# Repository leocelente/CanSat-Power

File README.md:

# CanSat - Power Board
## Introduction
These are the design files for the CanSat power distribution board
## Content
This repository contains the EAGLE project and the design block for the TLV62568 buck converter.
## Note
This was my first pcb design project and was not tested in any shape or form.

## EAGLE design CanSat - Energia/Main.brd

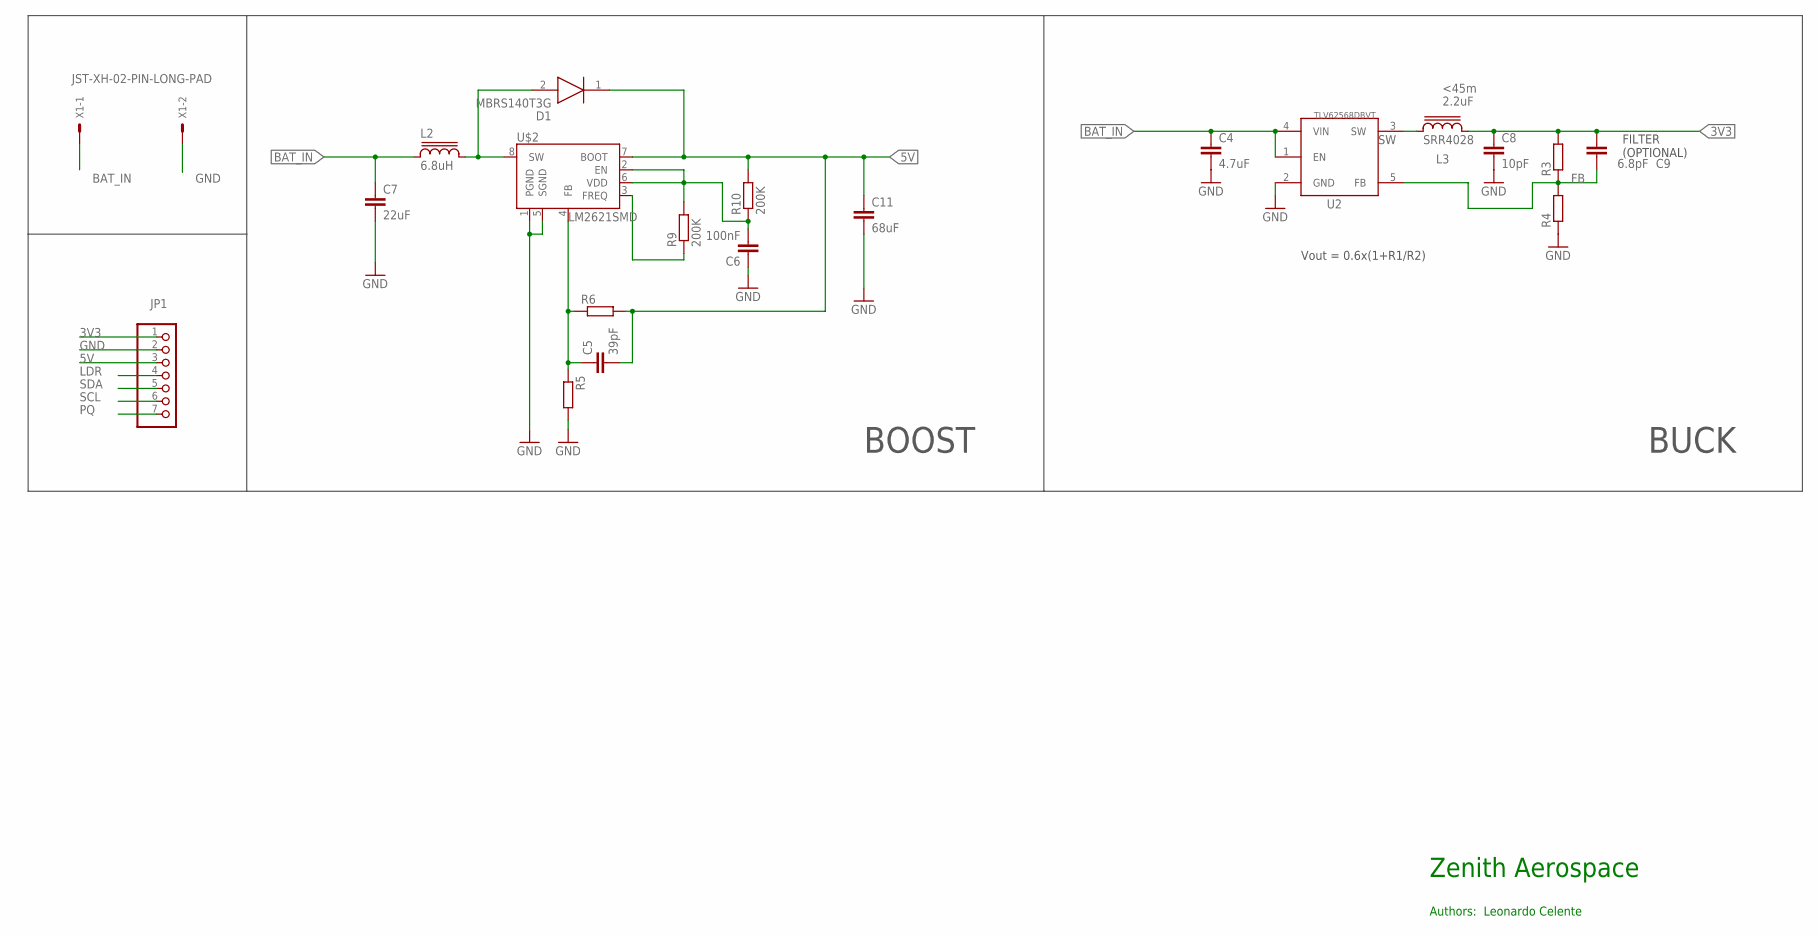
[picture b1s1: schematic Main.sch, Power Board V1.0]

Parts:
C4: 4.7uF; C0805
C5: 39pF; C0805
C6: 100nF; C0805
C7: 22uF; C1210
C8: 10pF; C0805
C9: 6.8pF; C0805
C11: 68uF; C1210
D1: MBRS140T3G; DIOM5436X247N
JP1: PINHD-1X7; 1X07
L2: 6.8uH; SRR1280
L3: SRR4028
R3, R4, R5, R6: R-EU_R0805; R0805
R9, R10: 200K; R0805
U2: TLV62568DBVT; SOT95P280X145-5N
U$2: LM2621SMD; MSOP-8
X1: JST-XH-02-PIN-LONG-PAD; JST-XH-02-PACKAGE-LONG-PAD

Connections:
3V3: C8.1, C9.1, JP1.1, L3.2, R3.2
5V: C5.2, C11.1, D1.1 (K), JP1.3, R6.2, R10.2, U$2.7 (BOOT)
BAT_IN: C4.1, C7.1, L2.1, U2.1 (EN), U2.4 (VIN), X1.1
FB: C9.2, R3.1, R4.2, U2.5 (FB)
GND: C4.2, C6.1, C7.2, C8.2, C11.2, JP1.2, R4.1, R5.2, U2.2 (GND), U$2.1 (PGND), U$2.5 (SGND), X1.2
LDR: JP1.4
unnamed: C5.1, R5.1, R6.1, U$2.4 (FB)
unnamed: D1.2 (A), L2.2, U$2.8 (SW)
unnamed: C6.2, R9.2, R10.1, U$2.2 (EN), U$2.6 (VDD)
unnamed: R9.1, U$2.3 (FREQ)
PQ: JP1.7
SCL: JP1.6
SDA: JP1.5
SW: L3.1, U2.3 (SW)

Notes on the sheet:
FILTER (OPTIONAL)
Vout = 0.6x(1+R1/R2)
BUCK
BOOST
Zenith Aerospace
Authors: Leonardo Celente

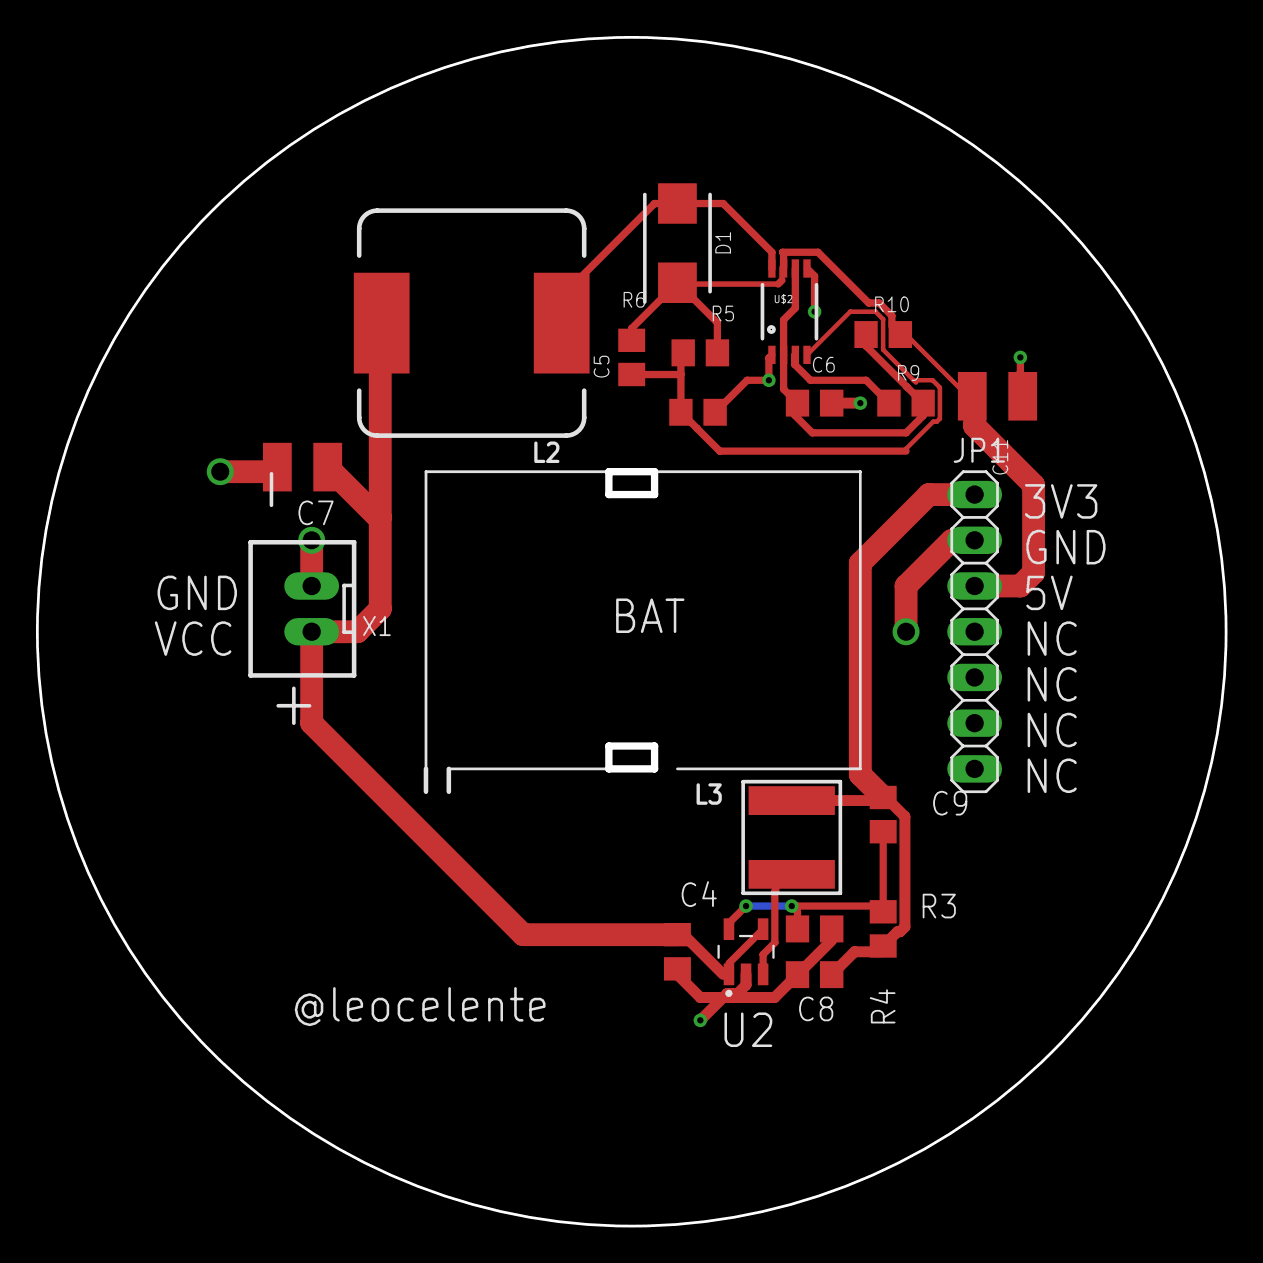
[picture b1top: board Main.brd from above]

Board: 2 copper layers, 65.8 x 65.8 mm, 20 parts (0 on the bottom side), 10 nets.

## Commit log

2020-06-03 added schematic pdf

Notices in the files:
parts and their libraries:
inductor-bourns: Copyright (C) 2008, Bob Starr
SparkFun-PowerIC: Licensing: Creative Commons ShareAlike 4.0 International - https://creativecommons.org/licenses/by-sa/4.0
